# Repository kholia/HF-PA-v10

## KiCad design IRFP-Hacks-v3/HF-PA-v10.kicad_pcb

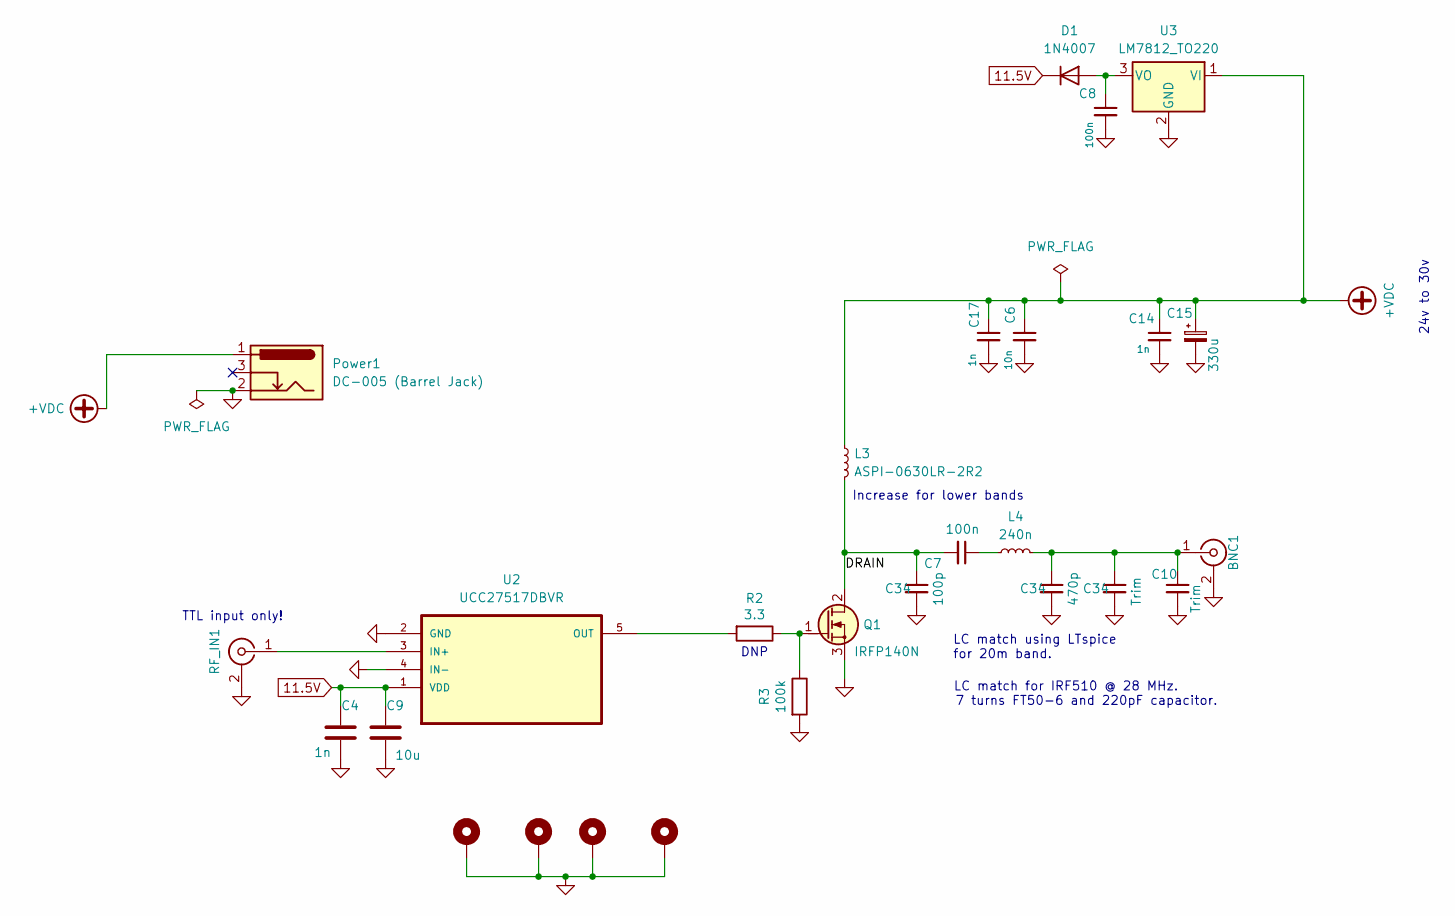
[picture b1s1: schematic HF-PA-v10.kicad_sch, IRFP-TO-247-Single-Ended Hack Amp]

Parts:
BNC1: SMA; SMA_Samtec_SMA-J-P-X-ST-EM1_EdgeMount
C4, C14, C17: 1n; C_1206_3216Metric_Pad1.33x1.80mm_HandSolder
C6: 10n; C_1206_3216Metric_Pad1.33x1.80mm_HandSolder
C7, C8: 100n; C_1206_3216Metric_Pad1.33x1.80mm_HandSolder
C9: 10u; C_1206_3216Metric_Pad1.33x1.80mm_HandSolder
C10: Trim; C_1206_3216Metric_Pad1.33x1.80mm_HandSolder
C15: 330u; CP_Radial_D8.0mm_P5.00mm
C34: 100p; C_1206_3216Metric_Pad1.33x1.80mm_HandSolder
D1: 1N4007; D_DO-41_SOD81_P2.54mm_Vertical_KathodeUp
H1, H2, H3, H4: MountingHole_Pad; MountingHole_3.2mm_M3_Pad_Via
L3: ASPI-0630LR-2R2; L_7.3x7.3_H3.5
L4: 240n; L_Toroid_Vertical_L10.0mm_W5.0mm_P5.08mm
Power1: DC-005 (Barrel Jack); XKB_DC-005-5A-2.0_Modded
Q1: IRFP140N; TO-247-3_Horizontal_TabDown_Modded
R2: 3.3; R_1206_3216Metric_Pad1.30x1.75mm_HandSolder
R3: 100k; R_1206_3216Metric_Pad1.30x1.75mm_HandSolder
RF_IN1: SMA; SMA_Samtec_SMA-J-P-X-ST-EM1_EdgeMount
U2: UCC27517DBVR; SOT-23-5_HandSoldering
U3: LM7812_TO220; TO-220-3_Horizontal_TabDown

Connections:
11.5V: C4.1, C9.1, D1.1 (K), U2.1 (VDD)
+VDC: C6.1, C14.1, C15.1, C17.1, L3.1, Power1.1, U3.1 (VI)
/DRAIN: C7.2, L3.2, Q1.2 (D); also elsewhere on the board
GND: C4.2, C6.2, C8.2, C9.2, C10.2, C14.2, C15.2, C17.2, H1.1, H2.1, H3.1, H4.1, Power1.2, Q1.3 (S), R3.2, RF_IN1.2 (Ext), U2.2 (GND), U2.4 (IN-), U3.2 (GND); also elsewhere on the board
unnamed: C7.1, L4.1
unnamed: C8.1, D1.2 (A), U3.3 (VO)
unnamed: Q1.1 (G), R2.1, R3.1
unnamed: RF_IN1.1 (In), U2.3 (IN+)
unnamed 8: C10.1, L4.2; also elsewhere on the board
unnamed: R2.2, U2.5 (OUT)

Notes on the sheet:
DNP
TTL input only!
LC match for IRF510 @ 28 MHz. 7 turns FT50-6 and 220pF capacitor.
LC match using LTspice for 20m band.
24v to 30v
Increase for lower bands

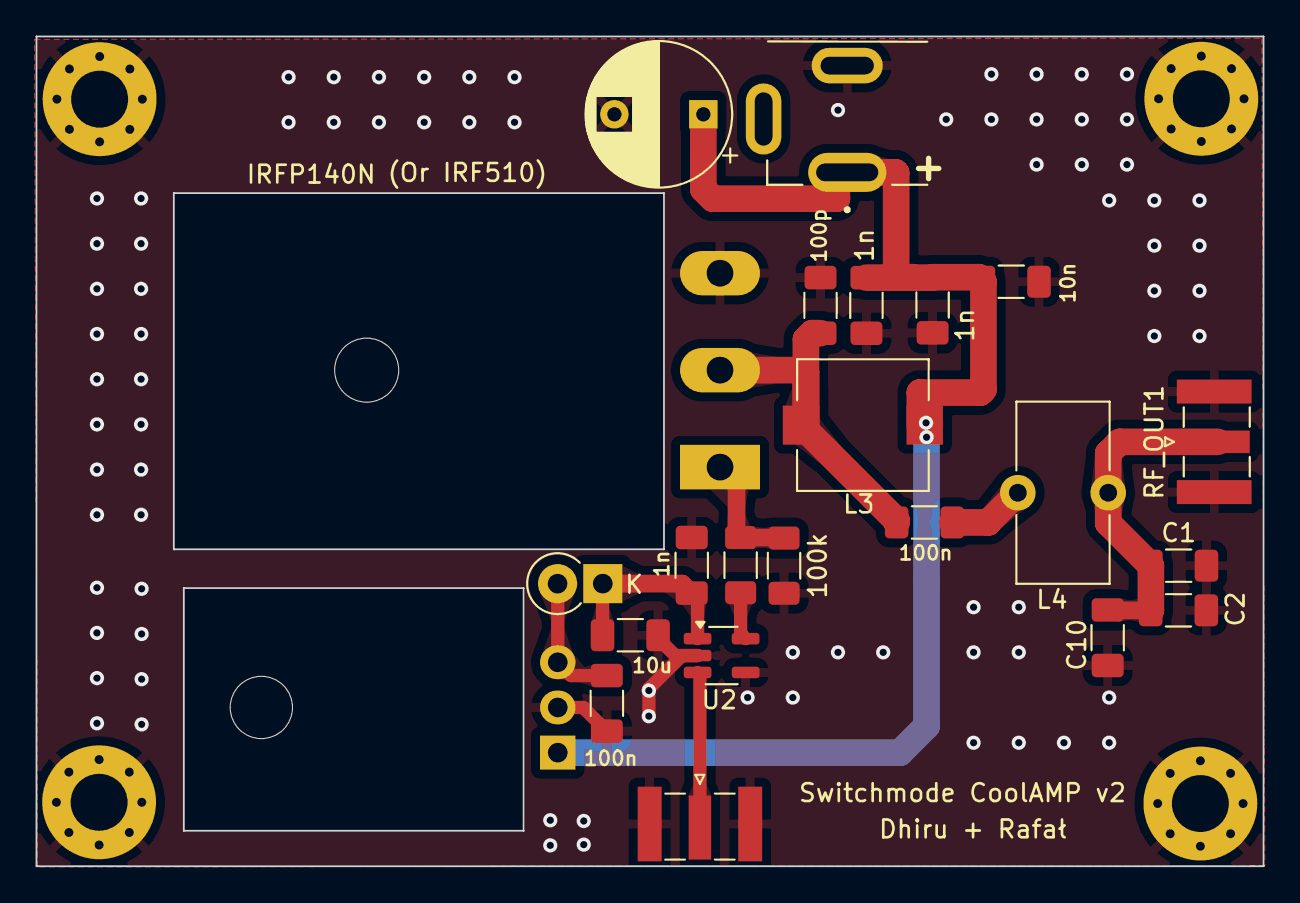
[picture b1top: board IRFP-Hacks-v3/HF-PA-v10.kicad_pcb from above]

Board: 2 copper layers, 69.0 x 46.6 mm, 27 parts (0 on the bottom side), 10 nets.

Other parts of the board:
C1: 470p; C_1206_3216Metric_Pad1.33x1.80mm_HandSolder
C2: Trim; C_1206_3216Metric_Pad1.33x1.80mm_HandSolder
C3: 100p; C_1206_3216Metric_Pad1.33x1.80mm_HandSolder
RF_OUT1: SMA; SMA_Samtec_SMA-J-P-X-ST-EM1_EdgeMount

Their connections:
/DRAIN: C3.1; also elsewhere on the board
GND: C1.2, C2.2, C3.2, RF_OUT1.2 (Ext); also elsewhere on the board
unnamed 8: C1.1, C2.1, RF_OUT1.1 (In); also elsewhere on the board

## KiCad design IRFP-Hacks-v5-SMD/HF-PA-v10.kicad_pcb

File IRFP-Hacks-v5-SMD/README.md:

This works great - tested in June 2024.

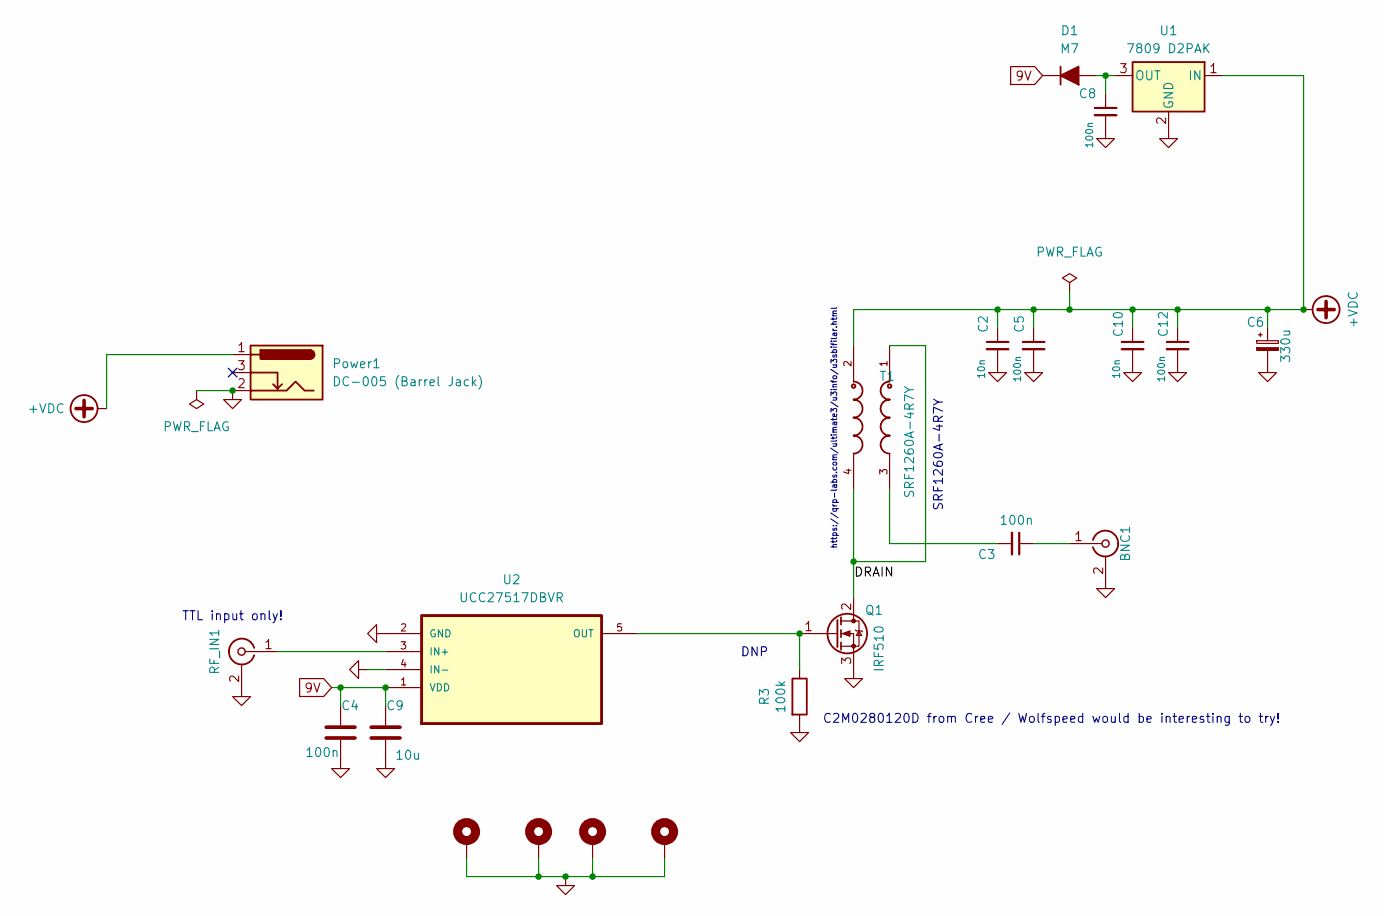
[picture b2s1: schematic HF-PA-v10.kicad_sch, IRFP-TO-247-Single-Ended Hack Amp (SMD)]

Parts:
BNC1: SMA; SMA_Samtec_SMA-J-P-H-ST-EM1_EdgeMount
C2, C10: 10n; C_1206_3216Metric_Pad1.33x1.80mm_HandSolder; LCSC Part C24783
C3, C4, C8: 100n; C_1206_3216Metric_Pad1.33x1.80mm_HandSolder; LCSC Part C110255
C5, C12: 100n; C_1206_3216Metric_Pad1.33x1.80mm_HandSolder; LCSC Part C55077
C6: 330u; CP_Radial_D8.0mm_P5.00mm
C9: 10u; C_1206_3216Metric_Pad1.33x1.80mm_HandSolder; LCSC Part C13585
D1: M7; D_SMA; LCSC Part C111122
H1, H2, H3, H4: MountingHole_Pad; MountingHole_3.2mm_M3_Pad_Via
Power1: DC-005 (Barrel Jack); XKB_DC-005-5A-2.0_Modded
Q1: IRF510; TO-247-3_Horizontal_TabDown_Modded
R3: 100k; R_1206_3216Metric_Pad1.30x1.75mm_HandSolder; LCSC Part C17900
RF_IN1: SMA; SMA_Samtec_SMA-J-P-H-ST-EM1_EdgeMount
T1: SRF1260A-4R7Y; IND_SRF1260A-4R7Y-Longer-Pads; LCSC Part C3273481
U1: 7809 D2PAK; TO-263-2-bigger; LCSC Part C54614
U2: UCC27517DBVR; TSOT-23-5_HandSoldering; LCSC Part C99395

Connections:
9V: C4.1, C9.1, D1.1 (K), U2.1 (VDD)
+VDC: C2.1, C5.1, C6.1, C10.1, C12.1, Power1.1, T1.2, U1.1 (IN)
/DRAIN: Q1.2 (D), T1.1, T1.4
GND: C2.2, C4.2, C5.2, C6.2, C8.2, C9.2, C10.2, C12.2, H1.1, H2.1, H3.1, H4.1, Power1.2, Q1.3 (S), R3.2, RF_IN1.2 (Ext), U1.2 (GND), U2.2 (GND), U2.4 (IN-); also elsewhere on the board
unnamed: C3.2, T1.3
unnamed: C8.1, D1.2 (A), U1.3 (OUT)
unnamed: Q1.1 (G), R3.1, U2.5 (OUT)
unnamed: RF_IN1.1 (In), U2.3 (IN+)
unnamed 8: C3.1; also elsewhere on the board

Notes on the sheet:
DNP
https://qrp-labs.com/ultimate3/u3info/u3sbifilar.html
SRF1260A-4R7Y
TTL input only!
C2M0280120D from Cree / Wolfspeed would be interesting to try!

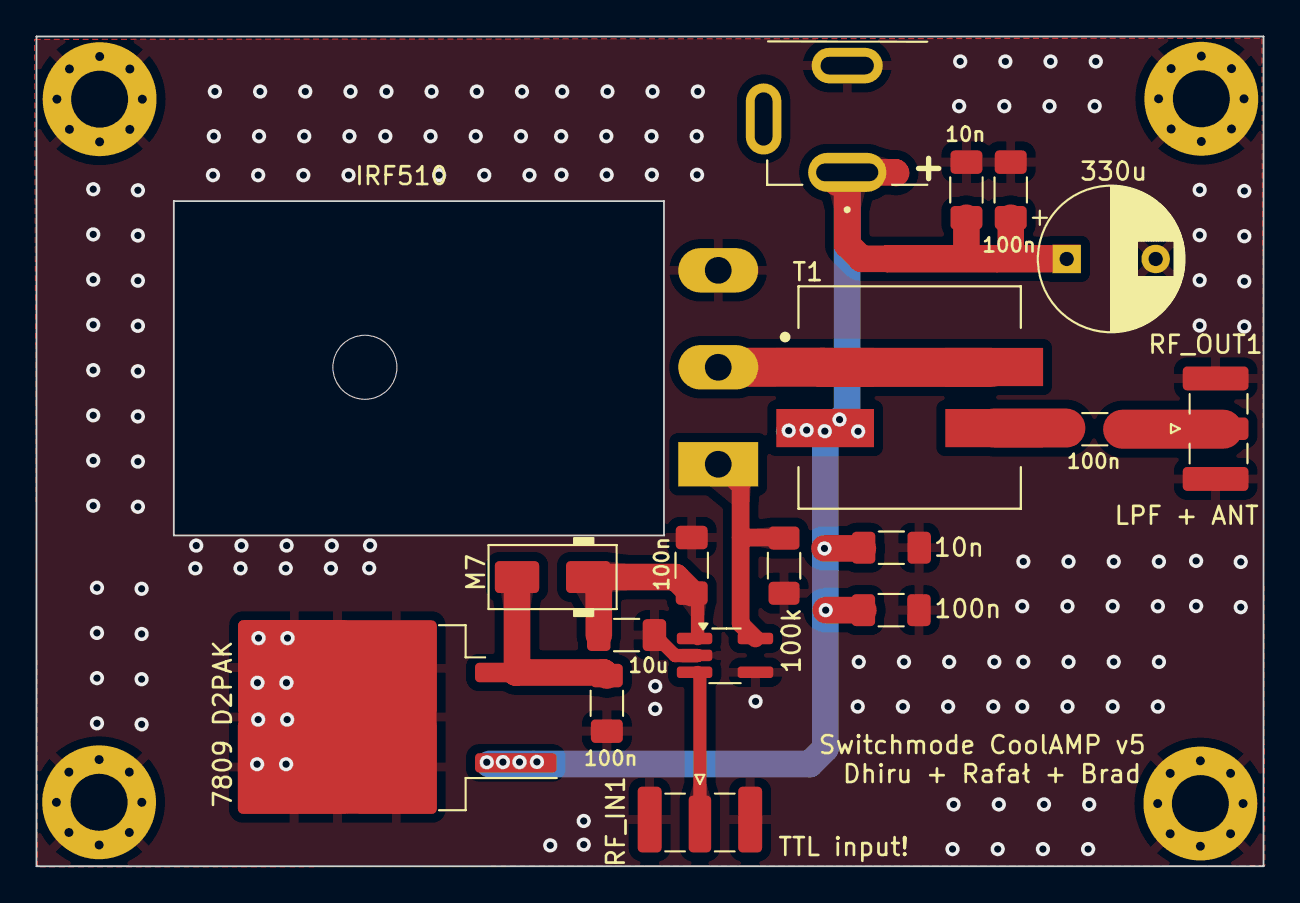
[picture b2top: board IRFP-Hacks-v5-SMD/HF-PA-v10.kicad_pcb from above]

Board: 2 copper layers, 69.0 x 46.6 mm, 22 parts (0 on the bottom side), 9 nets.

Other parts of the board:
RF_OUT1: SMA; SMA_Samtec_SMA-J-P-H-ST-EM1_EdgeMount

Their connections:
GND: RF_OUT1.2 (Ext); also elsewhere on the board
unnamed 8: RF_OUT1.1 (In); also elsewhere on the board

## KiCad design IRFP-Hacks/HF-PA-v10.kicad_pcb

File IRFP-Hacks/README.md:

IRF530 hack. ~1.5W in, 20W+ out on 20m @ 25v to 30v drain.

ATTENTION: Use a fast fan when doing digital modes using this PA.

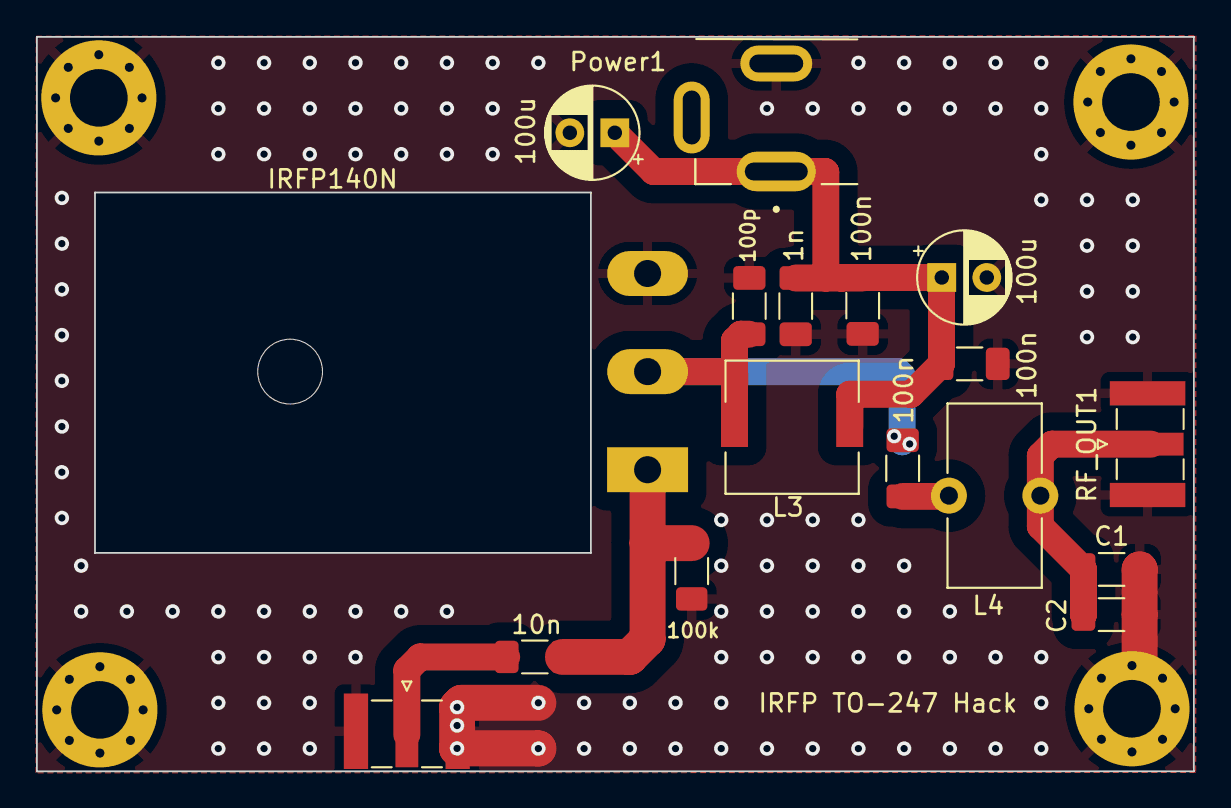
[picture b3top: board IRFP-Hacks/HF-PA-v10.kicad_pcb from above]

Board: 2 copper layers, 64.3 x 40.8 mm, 21 parts (0 on the bottom side), 7 nets.

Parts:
C1: 470p; C_1206_3216Metric_Pad1.33x1.80mm_HandSolder
C2: Trim; C_1206_3216Metric_Pad1.33x1.80mm_HandSolder
C3: 100p; C_1206_3216Metric_Pad1.33x1.80mm_HandSolder
C5, C15: 100u; CP_Radial_D5.0mm_P2.50mm
C6, C7, C14: 100n; C_1206_3216Metric_Pad1.33x1.80mm_HandSolder
C17: 1n; C_1206_3216Metric_Pad1.33x1.80mm_HandSolder
C19: 10n; C_1206_3216Metric_Pad1.33x1.80mm_HandSolder
H1, H2, H3, H4: MountingHole_Pad; MountingHole_3.2mm_M3_Pad_Via
L3: 3.3uH / 4.7uH; L_7.3x7.3_H3.5
L4: 240n; L_Toroid_Vertical_L10.0mm_W5.0mm_P5.08mm
Power1: DC-005 (Barrel Jack); XKB_DC-005-5A-2.0_Modded
Q1: IRFP140N; TO-247-3_Horizontal_TabDown_Modded
R1: 100k; R_1206_3216Metric_Pad1.30x1.75mm_HandSolder
RF_IN1: SMA; SMA_Samtec_SMA-J-P-X-ST-EM1_EdgeMount
RF_OUT1: SMA; SMA_Samtec_SMA-J-P-X-ST-EM1_EdgeMount

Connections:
+VDC: C5.1, C6.1, C14.1, C15.1, C17.1, L3.1, Power1.1
/DRAIN: C3.1, C7.2, L3.2, Q1.2 (D)
GND: C1.2, C2.2, C3.2, C5.2, C6.2, C14.2, C15.2, C17.2, H1.1, H2.1, H3.1, H4.1, Power1.2, Q1.3 (S), R1.2, RF_IN1.2 (Ext), RF_OUT1.2 (Ext)
unnamed: C7.1, L4.1
unnamed: C19.2, Q1.1 (G), R1.1
unnamed: C19.1, RF_IN1.1 (In)
unnamed: C1.1, C2.1, L4.2, RF_OUT1.1 (In)

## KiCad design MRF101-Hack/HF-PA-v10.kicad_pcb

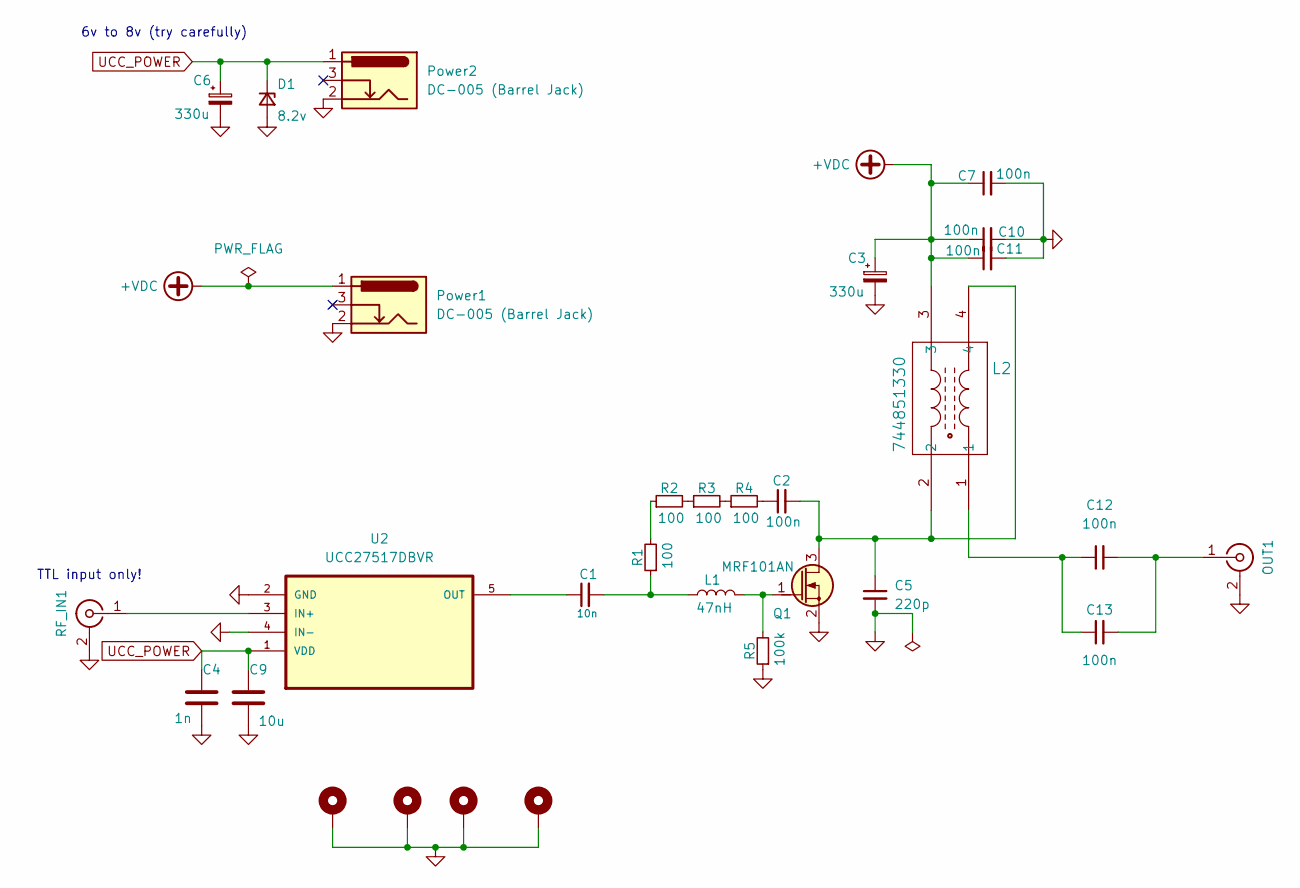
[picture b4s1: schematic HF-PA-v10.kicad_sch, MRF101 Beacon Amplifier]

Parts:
C1: 10n; C_1206_3216Metric_Pad1.33x1.80mm_HandSolder
C2, C7, C10, C11, C12, C13: 100n; C_1206_3216Metric_Pad1.33x1.80mm_HandSolder
C3, C6: 330u; C_Radial_D10.0mm_H12.5mm_P5.00mm
C4: 1n; C_1206_3216Metric_Pad1.33x1.80mm_HandSolder
C5: 220p; C_1206_3216Metric_Pad1.33x1.80mm_HandSolder
C9: 10u; C_1206_3216Metric_Pad1.33x1.80mm_HandSolder
D1: 8.2v; D_DO-35_SOD27_P3.81mm_Vertical_KathodeUp
H1, H2, H3, H4: MountingHole_Pad; MountingHole_3.2mm_M3_Pad_Via
L1: 47nH; WE-CAIR_4248
L2: 744851330; 744851330_WRE
OUT1: SMA; SMA_Samtec_SMA-J-P-X-ST-EM1_EdgeMount
Power1, Power2: DC-005 (Barrel Jack); XKB_DC-005-5A-2.0_Modded
Q1: MRF101AN; TO-220-3_Horizontal_TabDown
R1, R2, R3, R4: 100; R_2512_6332Metric_Pad1.40x3.35mm_HandSolder
R5: 100k; R_2512_6332Metric_Pad1.40x3.35mm_HandSolder
RF_IN1: SMA; SMA_Samtec_SMA-J-P-X-ST-EM1_EdgeMount
U2: UCC27517DBVR; SOT-23-5_HandSoldering

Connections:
+VDC: C3.1, C7.1, C10.1, C11.1, L2.3, Power1.1
GND: C3.2, C4.2, C5.2, C6.2, C7.2, C9.2, C10.2, C11.2, D1.2 (A), H1.1, H2.1, H3.1, H4.1, OUT1.2 (Ext), Power1.2, Power2.2, Q1.2 (S), R5.1, RF_IN1.2 (Ext), U2.2 (GND), U2.4 (IN-)
unnamed: C1.2, L1.1, R1.1
unnamed: C2.1, R4.2
unnamed: C12.1, C13.1, L2.1
unnamed: C12.2, C13.2, OUT1.1 (In)
unnamed: C2.2, C5.1, L2.2, L2.4, Q1.3 (D)
unnamed: L1.2, Q1.1 (G), R5.2
unnamed: R1.2, R2.1
unnamed: R2.2, R3.1
unnamed: R3.2, R4.1
unnamed: RF_IN1.1 (In), U2.3 (IN+)
unnamed: C1.1, U2.5 (OUT)
UCC_POWER: C4.1, C6.1, C9.1, D1.1 (K), Power2.1, U2.1 (VDD)

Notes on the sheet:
TTL input only!
6v to 8v (try carefully)

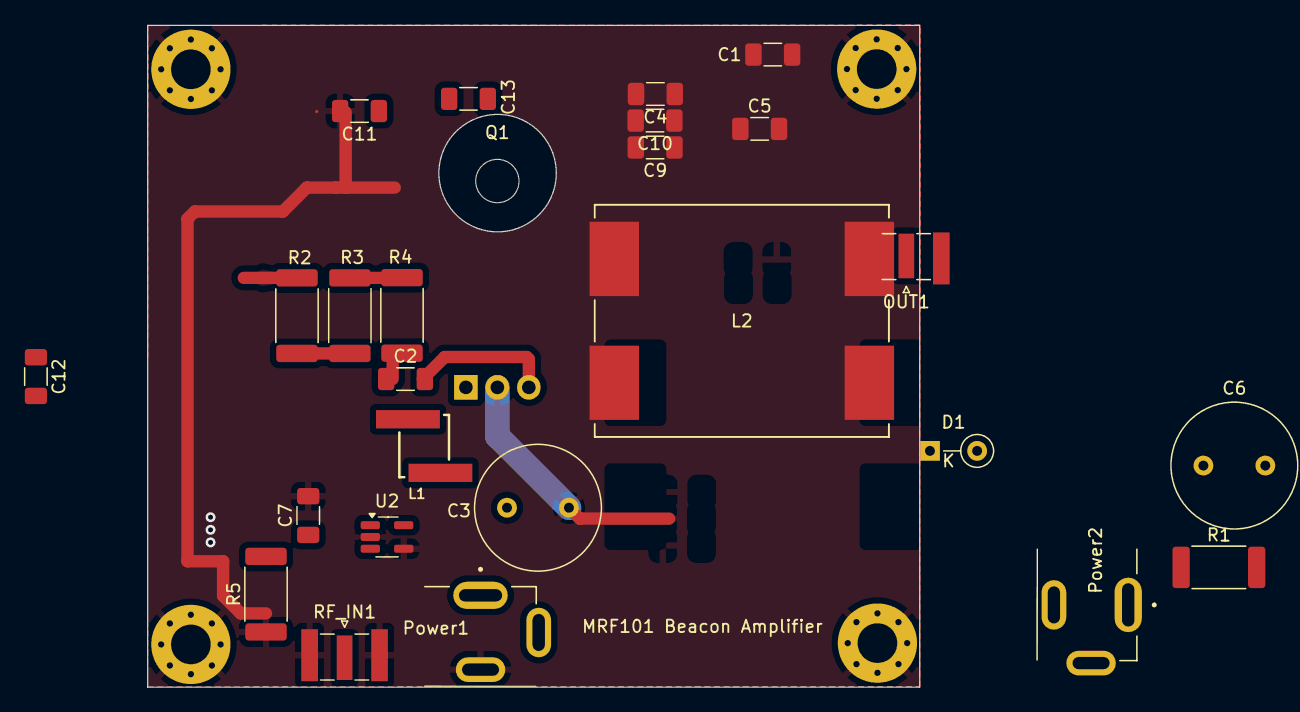
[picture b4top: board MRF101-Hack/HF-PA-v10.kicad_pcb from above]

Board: 2 copper layers, 62.3 x 53.4 mm, 30 parts (0 on the bottom side), 14 nets.

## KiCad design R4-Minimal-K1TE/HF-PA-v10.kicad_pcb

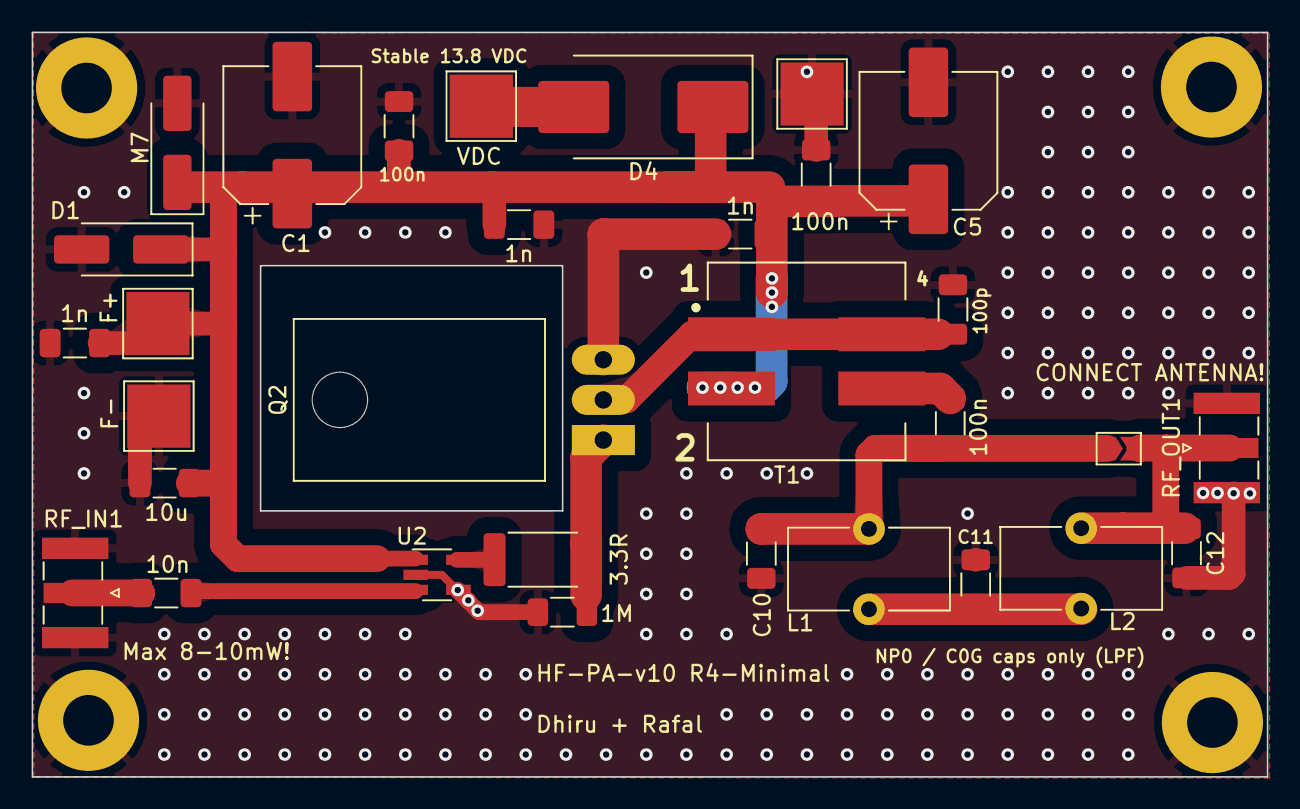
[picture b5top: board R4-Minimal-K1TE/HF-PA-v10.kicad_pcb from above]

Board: 2 copper layers, 78.1 x 47.1 mm, 35 parts (0 on the bottom side), 12 nets.

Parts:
C1, C5: 220u; CP_Elec_8x10.5
C2, C4, C17: 1n; C_1206_3216Metric_Pad1.33x1.80mm_HandSolder
C3: 100p; C_1206_3216Metric_Pad1.33x1.80mm_HandSolder
C6, C7, C14: 100n; C_1206_3216Metric_Pad1.33x1.80mm_HandSolder
C10, C12: 120p; C_1206_3216Metric_Pad1.33x1.80mm_HandSolder
C11: 200p; C_1206_3216Metric_Pad1.33x1.80mm_HandSolder
C16: 10u; C_1206_3216Metric_Pad1.33x1.80mm_HandSolder
C19: 10n; C_1206_3216Metric_Pad1.33x1.80mm_HandSolder
D1: 18v; D_SMA_Handsoldering
D2: M7; D_SMA_Handsoldering
D4: 2A+ Schottky (SS34 or similar); D_SMC_Handsoldering
Fan+1: F+; TestPoint_Pad_4.0x4.0mm
Fan-1: F-; TestPoint_Pad_4.0x4.0mm
H1, H2, H3, H4: MountingHole_Pad; MountingHole_3.2mm_M3_Pad
JP1: Jumper_2_Open; SolderJumper-2_P1.3mm_Open_TrianglePad1.0x1.5mm
L1, L2: 360n; L_Toroid_Vertical_L10.0mm_W5.0mm_P5.08mm
PI1: VDC; TestPoint_Pad_4.0x4.0mm
PI2: GND; TestPoint_Pad_4.0x4.0mm
Q2: IRF510; TO-220-3_Horizontal_TabDown
R1: 1M; R_1206_3216Metric_Pad1.30x1.75mm_HandSolder
R3: 3.3R; R_2512_6332Metric_Pad1.40x3.35mm_HandSolder
RF_IN1: SMA; SMA_Samtec_SMA-J-P-X-ST-EM1_EdgeMount
RF_OUT1: SMA; SMA_Samtec_SMA-J-P-X-ST-EM1_EdgeMount
T1: Bifilar XFMR; IND_SRF1260A-4R7Y-Longer-Pads
U2: UCC27517DBVR; SOT-23-5_HandSoldering

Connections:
12V: C1.1, C2.1, C4.1, C5.1, C6.1, C14.1, C16.1, C17.1, D1.1 (K), D2.1 (K), D4.1 (K), Fan+1.1, T1.2, U2.1 (VDD)
+VDC: D4.2 (A), PI1.1
/DRAIN: C3.1, Q2.2 (D), T1.1, T1.4
GND: C1.2, C2.2, C3.2, C4.2, C5.2, C6.2, C10.2, C11.2, C12.2, C14.2, C16.2, C17.2, D1.2 (A), D2.2 (A), Fan-1.1, H1.1, H2.1, H3.1, H4.1, PI2.1, Q2.3 (S), R1.2, RF_IN1.2 (Ext), RF_OUT1.2 (Ext), U2.2 (GND), U2.4 (IN-)
unnamed: C7.2, T1.3
unnamed: C11.1, L1.2, L2.1
unnamed: C7.1, C10.1, JP1.1 (A), L1.1
unnamed: C12.1, JP1.2 (B), L2.2, RF_OUT1.1 (In)
unnamed: Q2.1 (G), R1.1, R3.1
unnamed: C19.1, RF_IN1.1 (In)
unnamed: C19.2, U2.3 (IN+)
unnamed: R3.2, U2.5 (OUT)
